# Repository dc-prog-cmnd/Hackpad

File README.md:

# Hackpad
This is my hackpad for me to use while I'm gaming. Its name is Hackpado. 

# Schematic & PCB
The schematic and PCB were the first time I did anything like this, so I had A LOT of trouble. But I managed to get through it. 

Honestly, the PCB was pretty nice to design. The wiring was oddly satisfying to do. 

# Pieces
Hackpado comes in 2 pieces. The top and the bottom. 

# Assembly
The assembly is pretty easy since I only have 2 pieces to connect. :D

# BOM
5x white blank DSA keycaps
4x M3x16mm screws
4x M3x5mx4mm heatset inserts
2x SK6812 MINI-E LEDs
2x MX-Style switches
1 EC11 Rotary encoder
1 unsoldered Seeed XIAO RP2040

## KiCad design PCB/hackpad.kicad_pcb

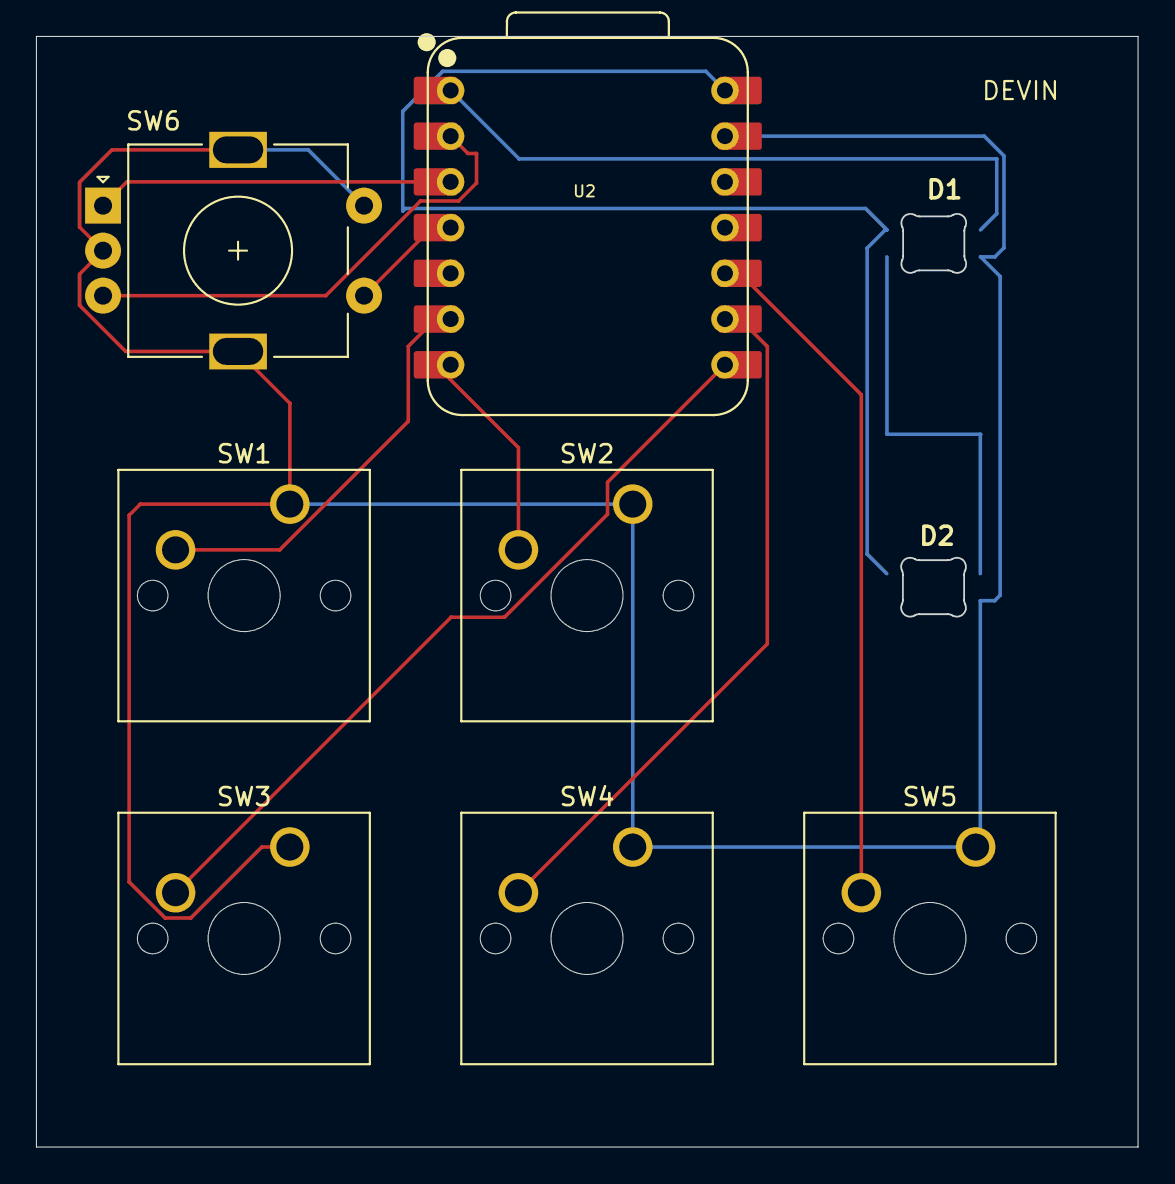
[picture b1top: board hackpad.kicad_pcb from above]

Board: 2 copper layers, 61.2 x 61.7 mm, 9 parts (0 on the bottom side), 12 nets.

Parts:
D1, D2: SK6812MINI-E; SK6812MINI-E_fixed
SW1, SW2, SW3, SW4, SW5: SW_Push; SW_Cherry_MX_1.00u_PCB
SW6: RotaryEncoder_Switch_MP; RotaryEncoder_Alps_EC11E-Switch_Vertical_H20mm
U2: XIAO-RP2040-DIP

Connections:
+5V: D1.1 (VDD), D2.1 (VDD), U2.14 (VBUS)
GND: D1.3 (VSS), D2.3 (VSS), SW1.1, SW2.1, SW3.1, SW4.1, SW5.1, SW6.C, SW6.MP, SW6.S2, U2.13 (GND)
unnamed: D1.4 (DIN), U2.1 (GPIO26/ADC0/A0)
unnamed: D1.2 (DOUT), D2.4 (DIN)
unnamed: SW2.2, U2.7 (GPIO0/TX)
unnamed: SW3.2, U2.8 (GPIO1/RX)
unnamed: SW4.2, U2.9 (GPIO2/SCK)
unnamed: SW5.2, U2.10 (GPIO4/MISO)
unnamed: SW1.2, U2.6 (GPIO7/SCL)
unnamed: SW6.B, U2.2 (GPIO27/ADC1/A1)
unnamed: SW6.A, U2.3 (GPIO28/ADC2/A2)
unnamed: SW6.S1, U2.4 (GPIO29/ADC3/A3)
